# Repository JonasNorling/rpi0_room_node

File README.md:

# Raspberry Pi Zero Room Board

## Features

### IR transmitter and receiver

Pinout:
 - 11 - BMC17 - IR TX
 - 12 - BCM18 - IR RX

These should be the default pins for the lirc_rpi module.
Reference: https://github.com/Irdroid/Irdroid-Rpi

### One-wire

Pinout:
 - 7 - BCM4 - one-wire signal

This should be the default pin for the w1-gpio module.
Reference: https://pinout.xyz/pinout/1_wire#

### RFM69 module

Pinout:
 - 19 - SPI0 MOSI - MOSI
 - 21 - SPI0 MISO - MISO
 - 23 - SPI0 SCLK - SCLK
 - 24 - SPI0 CE0 - chip select
 - 22 - BCM25 - DIO 0
 - 18 - BCM24 - DIO 1
 - 16 - BCM23 - DIO 2
 - 15 - BCM22 - RST

References:

#### https://github.com/hallard/LoRasPI/blob/master/README.md
 - GPIO22 - RST
 - GPIO25 - DIO0 or DIO1 or DIO2
 - GPIO23 - LED
 - GPIO24 - LED

#### http://wiki.dragino.com/index.php?title=Lora/GPS_HAT
 - GPIO7 - DIO0
 - GPIO0 - RST

#### https://github.com/PiInTheSky/pits-hardware/blob/master/PiLoraGatewayV2.5.pdf
 - GPIO5 - data LED
 - GPIO24 - DIO5
 - GPIO25 - DIO0

https://github.com/kobuki/RFM69OOK/blob/master/RFM69OOK.cpp
https://github.com/SevenW/embapps/tree/master/ArduinoRFM69

### LEDs

 - 3 - BCM2 - LED1
 - 5 - BCM3 - LED2
 - 13 - BCM27 - LED3
 - 29 - BCM5 - LED red
 - 31 - BCM6 - LED green
 - 32 - BCM12 - LED blue

## Things to fix in next revision

- Add protection resistor on DIO 2 -- it can be bidirectional.
- Preferably resistors on all DIOs
- Add current limiting resistor on one-wire supply pin -- the devices don't draw much current at all and it makes sense to protect the RPi's supply from whatever environment the one-wire sensors are in.

- SMA connector footprint is too wide for my connector from Electrokit
- RFM69 footprint is too wide
- SMA sits in a bad position for a RPi3

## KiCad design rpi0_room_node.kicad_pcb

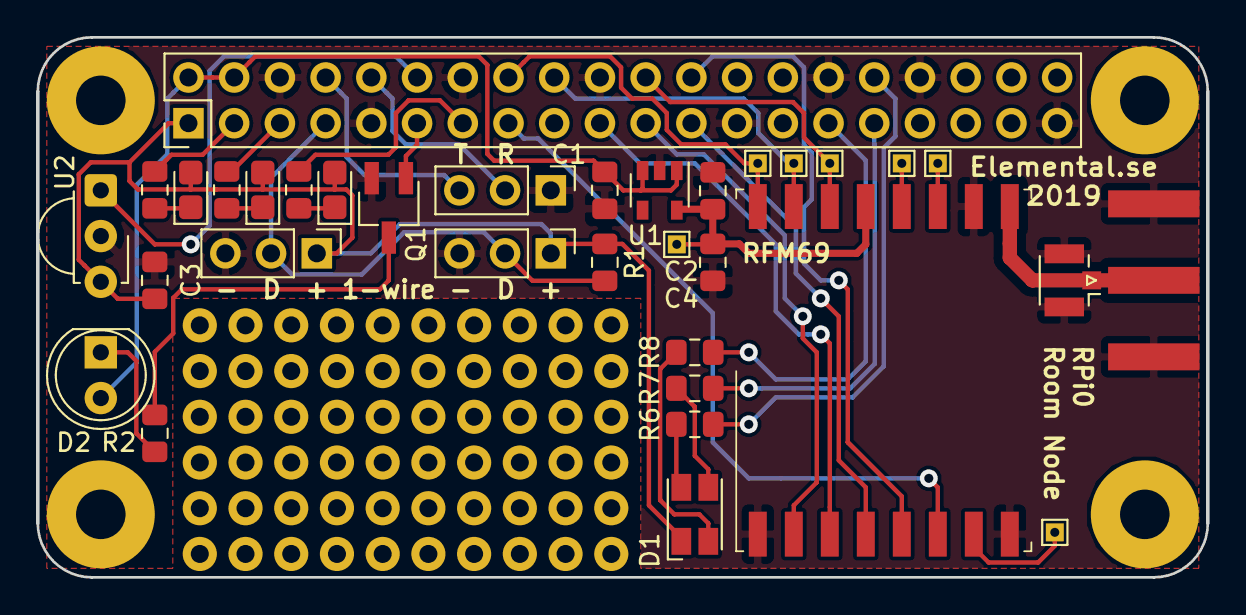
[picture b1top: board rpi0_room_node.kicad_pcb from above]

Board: 2 copper layers, 65.0 x 30.0 mm, 38 parts (0 on the bottom side), 35 nets.

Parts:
AE1: SMA; SMA_Amphenol_132289_EdgeMount
AE2: U.FL; U.FL_Hirose_U.FL-R-SMT-1_Vertical
C1, C2, C4: C; C_0805_2012Metric_Pad1.15x1.40mm_HandSolder
C3: 1u; C_0805_2012Metric_Pad1.15x1.40mm_HandSolder
D1: ASMB-MTB0-0A3A2; LED_Avago_PLCC4_3.2x2.8mm_CW
D2: CQY99; LED_D5.0mm_IRGrey
D3, D4, D5: LED; LED_0805_2012Metric_Castellated
H1, H2, H3, H4: MountingHole; hole_2.75
J1: Raspberry Pi; PinHeader_2x20_P2.54mm_Vertical
J2, J3, J4: Conn_01x03; PinHeader_1x03_P2.54mm_Vertical
Q1: PDTC123Y; SC-59_Handsoldering
R1: 4k7; R_0805_2012Metric_Pad1.15x1.40mm_HandSolder
R2, R3, R4, R5, R6, R7, R8: R; R_0805_2012Metric_Pad1.15x1.40mm_HandSolder
TP1, TP2, TP3, TP4, TP5, TP6, TP7: TestPoint; TestPoint_THTPad_1.0x1.0mm_Drill0.5mm
U1: AP2210K-3.3; SOT-23-5
U2: TSOP382xx; Vishay_MINICAST-3Pin
U3: RFM69HCW; HOPERF_RFM69HW

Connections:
+3V3: C3.1, D1.1, D3.2, D4.2, D5.2, J1.1, J2.1, J4.1, R1.1, U2.3
+5V: C1.1, D2.2, J1.2, J1.4, U1.1, U1.3
/ANT: AE1.1, AE2.1, U3.9
/CE0: J1.24, U3.5
/IRRX: J1.12, U2.1
/IRTX: J1.11, Q1.1
/LED1: J1.3, R3.1
/LED2: J1.5, R4.1
/LED3: J1.13, R5.1
/LEDB: J1.32, R6.1
/LEDG: J1.31, R7.1
/LEDR: J1.29, R8.1
/MISO: J1.21, U3.2
/MOSI: J1.19, U3.3
/ONEWIRE: J1.7, J2.2, J4.2, R1.2
/RFM_DIO0: J1.22, TP6.1, U3.14
/RFM_DIO1: J1.18, TP5.1, U3.15
/RFM_DIO2: J1.16, TP4.1, U3.16
/RFM_DIO3: TP3.1, U3.11
/RFM_DIO4: TP2.1, U3.12
/RFM_DIO5: TP1.1, U3.7
/RFM_RST: J1.15, U3.6
/RXD: J1.10, J3.2
/SCLK: J1.23, U3.4
/TXD: J1.8, J3.3
GND: AE1.2, AE2.2, C1.2, C2.2, C3.2, C4.2, J1.6, J1.9, J1.14, J1.20, J1.25, J1.30, J1.34, J1.39, J2.3, J3.1, J4.3, Q1.2, U1.2, U2.2, U3.1, U3.8, U3.10
unnamed: D1.2, R6.2
unnamed: D1.3, R7.2
unnamed: D1.4, R8.2
unnamed: D2.1, R2.1
unnamed: D3.1, R3.2
unnamed: D4.1, R4.2
unnamed: D5.1, R5.2
unnamed: Q1.3, R2.2
VDDA: C2.1, C4.1, TP7.1, U1.5, U3.13

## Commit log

2019-01-02 Starting out
2019-01-02 Basic PCB layout
2019-01-02 Layouting
2019-01-02 README
2019-01-02 Add u.fl and second onewire header
2019-01-02 Add prototyping area
2019-01-02 Clean up silkscreen
2019-01-02 Silkscreen improvements
2019-01-05 Add test points, DIO 2
2019-01-05 Add testpoint, clean up
2019-01-05 Gerber options
2019-01-17 rev.A gerbers
2019-01-17 Component values and errata
2019-07-22 Experimental SKiDL representation
2019-08-03 Create LICENSE
